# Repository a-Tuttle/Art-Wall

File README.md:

# Wall-Art

## software
Software for the Wall-Art controllers.

## hardware
Sketches for printing PCBs.

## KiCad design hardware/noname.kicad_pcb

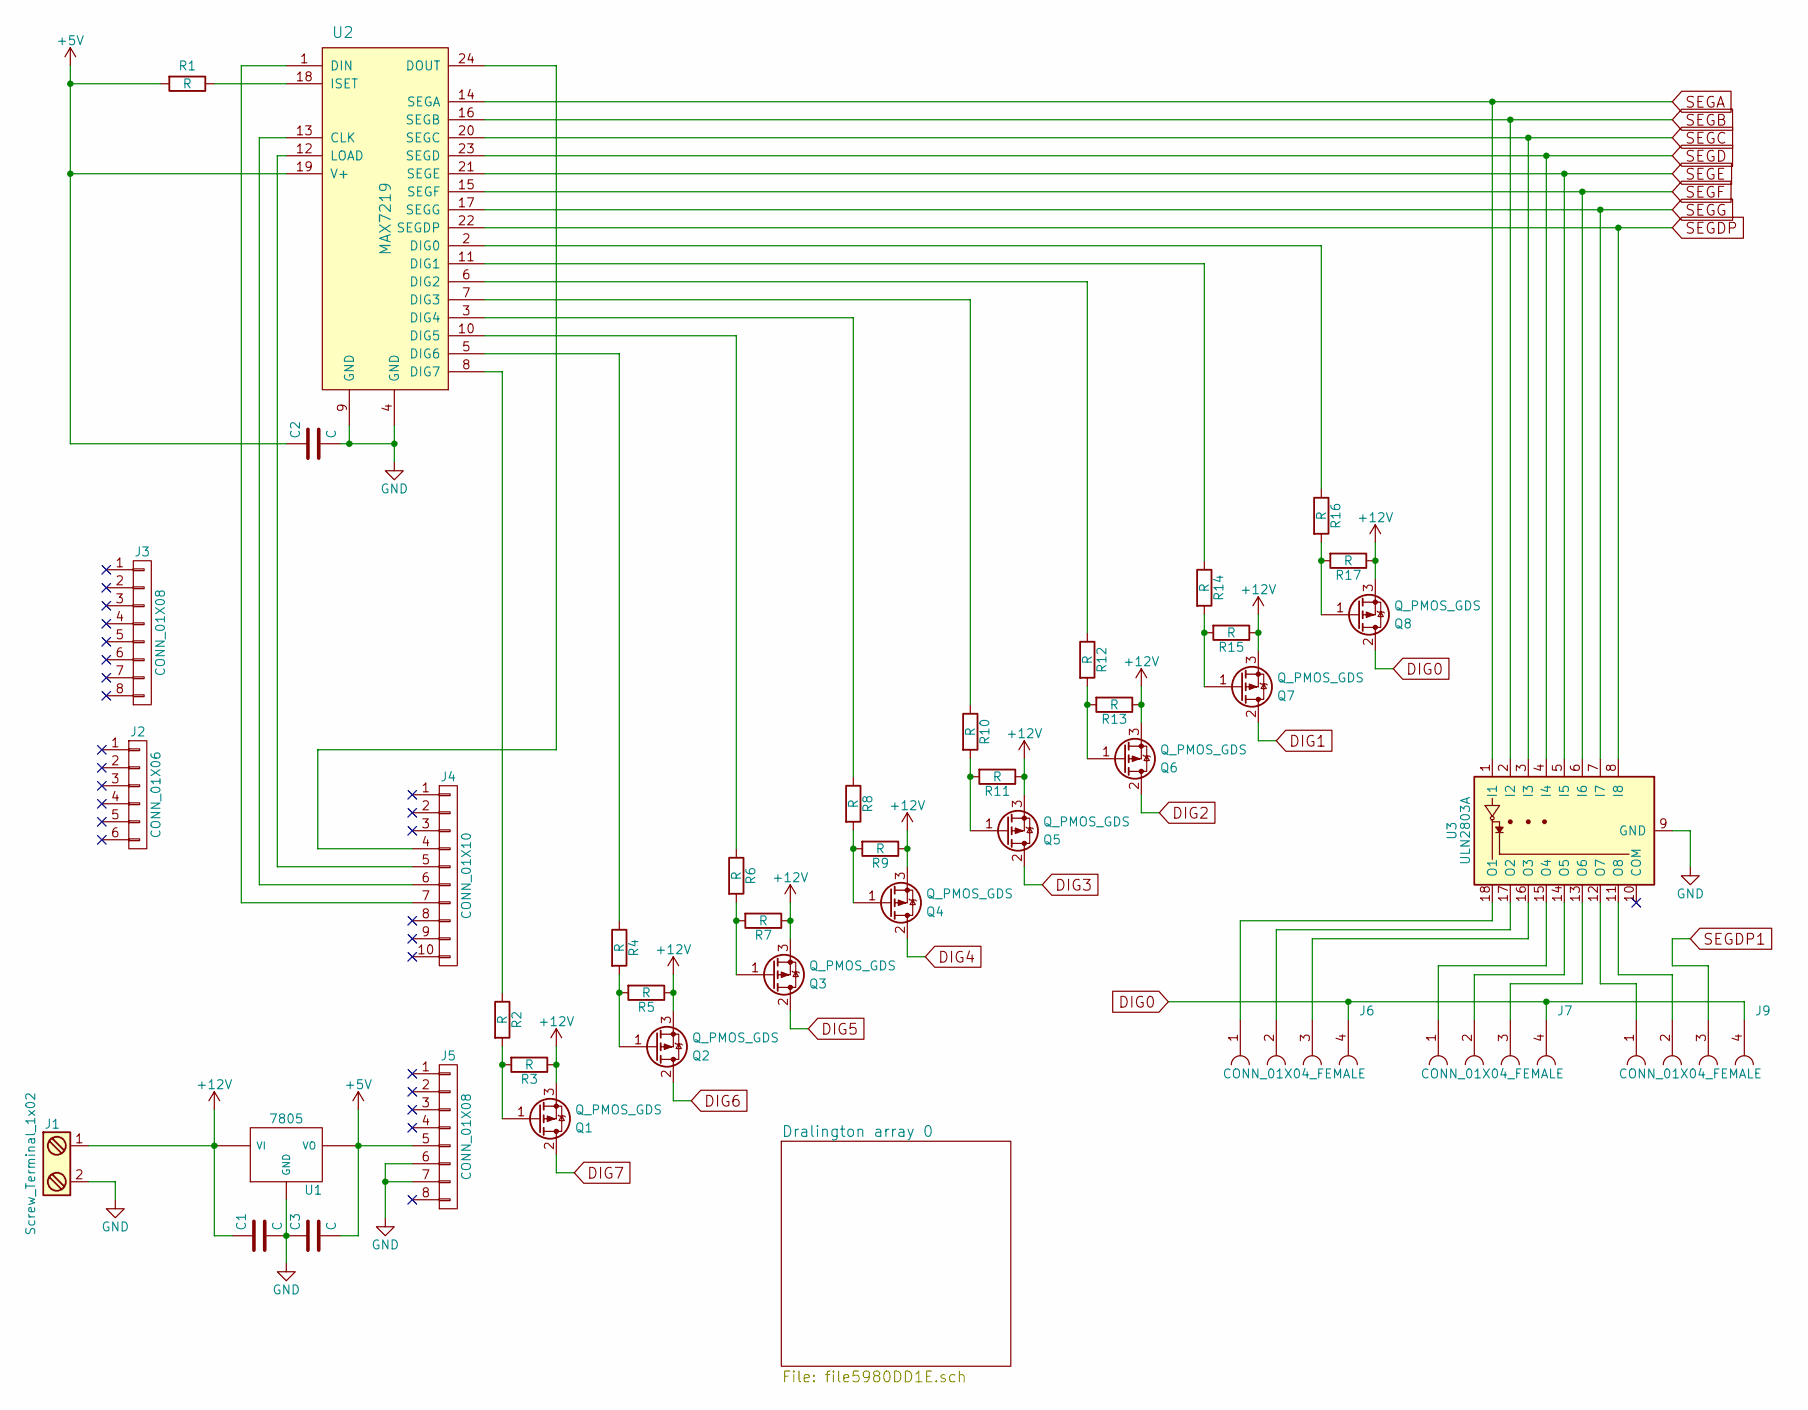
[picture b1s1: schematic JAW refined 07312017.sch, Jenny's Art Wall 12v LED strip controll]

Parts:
C1, C2, C3: C; C_Disc_D5.0mm_W2.5mm_P5.00mm
J1: Screw_Terminal_1x02; TerminalBlock_Philmore_TB132_02x5mm_Straight_power
J2: CONN_01X06; Pin_Header_Straight_1x06_Pitch2.54mm
J3, J5: CONN_01X08; Pin_Header_Straight_1x08_Pitch2.54mm
J4: CONN_01X10; Pin_Header_Straight_1x10_Pitch2.54mm
J6, J7, J9: CONN_01X04_FEMALE; Socket_Strip_Straight_1x04_Pitch2.54mm
Q1, Q2, Q3, Q4, Q5, Q6, Q7, Q8: Q_PMOS_GDS; TO-220
R1, R3, R5, R7, R9, R11, R13, R15, R17: R; R_Axial_DIN0309_L9.0mm_D3.2mm_P12.70mm_Horizontal
R2: R; R_Axial_DIN0207_L6.3mm_D2.5mm_P10.16mm_Horizontal
R4: R; R_Axial_DIN0204_L3.6mm_D1.6mm_P7.62mm_Horizontal
R6, R8, R10, R12, R14, R16: R; R_Axial_DIN0204_L3.6mm_D1.6mm_P5.08mm_Horizontal
U1: 7805; TO-220
U2: MAX7219; DIP-24_W7.62mm
U3: ULN2803A; DIP-18_W7.62mm

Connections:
+5V: C2.1, C3.2, J5.5, R1.2, U1.VO, U2.19 (V+)
+12V: C1.1, J1.1 (+), Q1.3 (S), Q2.3 (S), Q3.3 (S), Q4.3 (S), Q5.3 (S), Q6.3 (S), Q7.3 (S), Q8.3 (S), R3.1, R5.1, R7.1, R9.1, R11.1, R13.1, R15.1, R17.1, U1.VI
DIG0: J6.4, J7.4, J9.4, Q8.2 (D)
DIG1: Q7.2 (D); also elsewhere on the board
DIG2: Q6.2 (D); also elsewhere on the board
DIG3: Q5.2 (D); also elsewhere on the board
DIG4: Q4.2 (D); also elsewhere on the board
DIG5: Q3.2 (D); also elsewhere on the board
DIG6: Q2.2 (D); also elsewhere on the board
DIG7: Q1.2 (D); also elsewhere on the board
GND: C1.2, C2.2, C3.1, J1.2 (-), J5.6, J5.7, U1.GND, U2.4 (GND), U2.9 (GND), U3.9 (GND); also elsewhere on the board
unnamed: J4.5, U2.12 (LOAD)
unnamed: J4.6, U2.13 (CLK)
unnamed: J4.7, U2.1 (DIN)
unnamed: J6.1, U3.18 (O1)
unnamed: J6.2, U3.17 (O2)
unnamed: J6.3, U3.16 (O3)
unnamed: J7.1, U3.15 (O4)
unnamed: J7.2, U3.14 (O5)
unnamed: J7.3, U3.13 (O6)
unnamed: J9.1, U3.12 (O7)
unnamed: J9.2, U3.11 (O8)
unnamed: Q1.1 (G), R2.2, R3.2
unnamed: Q2.1 (G), R4.2, R5.2
unnamed: Q3.1 (G), R6.2, R7.2
unnamed: Q4.1 (G), R8.2, R9.2
unnamed: Q5.1 (G), R10.2, R11.2
unnamed: Q6.1 (G), R12.2, R13.2
unnamed: Q7.1 (G), R14.2, R15.2
unnamed: Q8.1 (G), R16.2, R17.2
unnamed: R1.1, U2.18 (ISET)
unnamed: R2.1, U2.8 (DIG7)
unnamed: R4.1, U2.5 (DIG6)
unnamed: R6.1, U2.10 (DIG5)
unnamed: R8.1, U2.3 (DIG4)
unnamed: R10.1, U2.7 (DIG3)
unnamed: R12.1, U2.6 (DIG2)
unnamed: R14.1, U2.11 (DIG1)
unnamed: R16.1, U2.2 (DIG0)
SEGA: U2.14 (SEGA), U3.1 (I1); also elsewhere on the board
SEGB: U2.16 (SEGB), U3.2 (I2); also elsewhere on the board
SEGC: U2.20 (SEGC), U3.3 (I3); also elsewhere on the board
SEGD: U2.23 (SEGD), U3.4 (I4); also elsewhere on the board
SEGDP: U2.22 (SEGDP), U3.8 (I8); also elsewhere on the board
SEGDP1: J9.3; also elsewhere on the board
SEGE: U2.21 (SEGE), U3.5 (I5); also elsewhere on the board
SEGF: U2.15 (SEGF), U3.6 (I6); also elsewhere on the board
SEGG: U2.17 (SEGG), U3.7 (I7); also elsewhere on the board

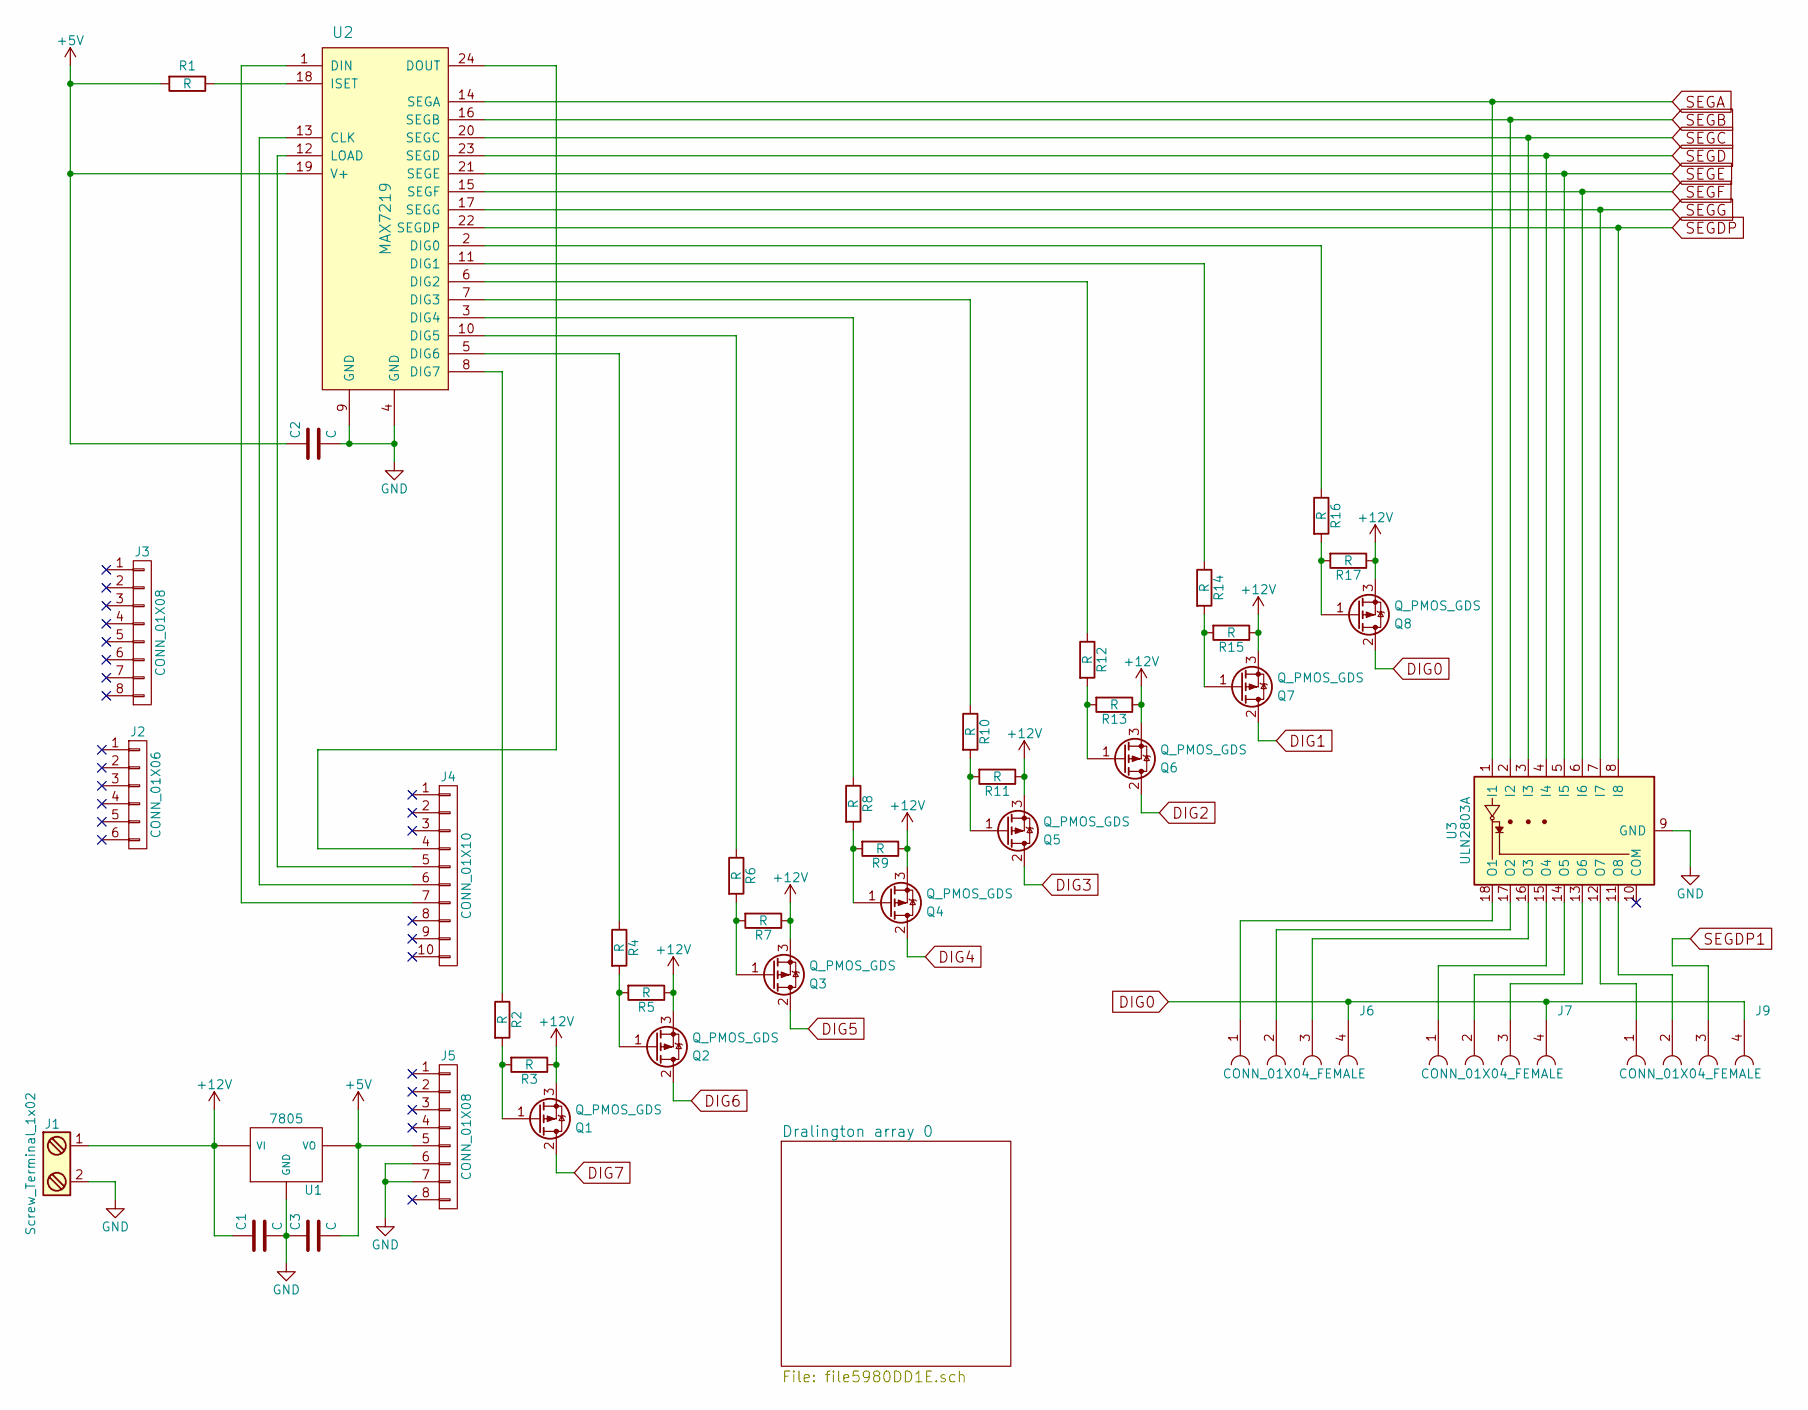
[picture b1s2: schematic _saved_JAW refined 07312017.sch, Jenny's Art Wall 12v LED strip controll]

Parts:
C1, C2, C3: C; C_Disc_D5.0mm_W2.5mm_P5.00mm
J1: Screw_Terminal_1x02; TerminalBlock_Philmore_TB132_02x5mm_Straight_power
J2: CONN_01X06; Pin_Header_Straight_1x06_Pitch2.54mm
J3, J5: CONN_01X08; Pin_Header_Straight_1x08_Pitch2.54mm
J4: CONN_01X10; Pin_Header_Straight_1x10_Pitch2.54mm
J6, J7, J9: CONN_01X04_FEMALE; Socket_Strip_Straight_1x04_Pitch2.54mm
Q1, Q2, Q3, Q4, Q5, Q6, Q7, Q8: Q_PMOS_GDS; TO-220
R1, R3, R5, R7, R9, R11, R13, R15, R17: R; R_Axial_DIN0309_L9.0mm_D3.2mm_P12.70mm_Horizontal
R2: R; R_Axial_DIN0207_L6.3mm_D2.5mm_P10.16mm_Horizontal
R4: R; R_Axial_DIN0204_L3.6mm_D1.6mm_P7.62mm_Horizontal
R6, R8, R10, R12, R14, R16: R; R_Axial_DIN0204_L3.6mm_D1.6mm_P5.08mm_Horizontal
U1: 7805; TO-220
U2: MAX7219; DIP-24_W7.62mm
U3: ULN2803A; DIP-18_W7.62mm

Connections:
+5V: C2.1, C3.2, J5.5, R1.2, U1.VO, U2.19 (V+)
+12V: C1.1, J1.1 (+), Q1.3 (S), Q2.3 (S), Q3.3 (S), Q4.3 (S), Q5.3 (S), Q6.3 (S), Q7.3 (S), Q8.3 (S), R3.1, R5.1, R7.1, R9.1, R11.1, R13.1, R15.1, R17.1, U1.VI
DIG0: J6.4, J7.4, J9.4, Q8.2 (D)
DIG1: Q7.2 (D); also elsewhere on the board
DIG2: Q6.2 (D); also elsewhere on the board
DIG3: Q5.2 (D); also elsewhere on the board
DIG4: Q4.2 (D); also elsewhere on the board
DIG5: Q3.2 (D); also elsewhere on the board
DIG6: Q2.2 (D); also elsewhere on the board
DIG7: Q1.2 (D); also elsewhere on the board
GND: C1.2, C2.2, C3.1, J1.2 (-), J5.6, J5.7, U1.GND, U2.4 (GND), U2.9 (GND), U3.9 (GND); also elsewhere on the board
unnamed: J4.5, U2.12 (LOAD)
unnamed: J4.6, U2.13 (CLK)
unnamed: J4.7, U2.1 (DIN)
unnamed: J6.1, U3.18 (O1)
unnamed: J6.2, U3.17 (O2)
unnamed: J6.3, U3.16 (O3)
unnamed: J7.1, U3.15 (O4)
unnamed: J7.2, U3.14 (O5)
unnamed: J7.3, U3.13 (O6)
unnamed: J9.1, U3.12 (O7)
unnamed: J9.2, U3.11 (O8)
unnamed: Q1.1 (G), R2.2, R3.2
unnamed: Q2.1 (G), R4.2, R5.2
unnamed: Q3.1 (G), R6.2, R7.2
unnamed: Q4.1 (G), R8.2, R9.2
unnamed: Q5.1 (G), R10.2, R11.2
unnamed: Q6.1 (G), R12.2, R13.2
unnamed: Q7.1 (G), R14.2, R15.2
unnamed: Q8.1 (G), R16.2, R17.2
unnamed: R1.1, U2.18 (ISET)
unnamed: R2.1, U2.8 (DIG7)
unnamed: R4.1, U2.5 (DIG6)
unnamed: R6.1, U2.10 (DIG5)
unnamed: R8.1, U2.3 (DIG4)
unnamed: R10.1, U2.7 (DIG3)
unnamed: R12.1, U2.6 (DIG2)
unnamed: R14.1, U2.11 (DIG1)
unnamed: R16.1, U2.2 (DIG0)
SEGA: U2.14 (SEGA), U3.1 (I1); also elsewhere on the board
SEGB: U2.16 (SEGB), U3.2 (I2); also elsewhere on the board
SEGC: U2.20 (SEGC), U3.3 (I3); also elsewhere on the board
SEGD: U2.23 (SEGD), U3.4 (I4); also elsewhere on the board
SEGDP: U2.22 (SEGDP), U3.8 (I8); also elsewhere on the board
SEGDP1: J9.3; also elsewhere on the board
SEGE: U2.21 (SEGE), U3.5 (I5); also elsewhere on the board
SEGF: U2.15 (SEGF), U3.6 (I6); also elsewhere on the board
SEGG: U2.17 (SEGG), U3.7 (I7); also elsewhere on the board

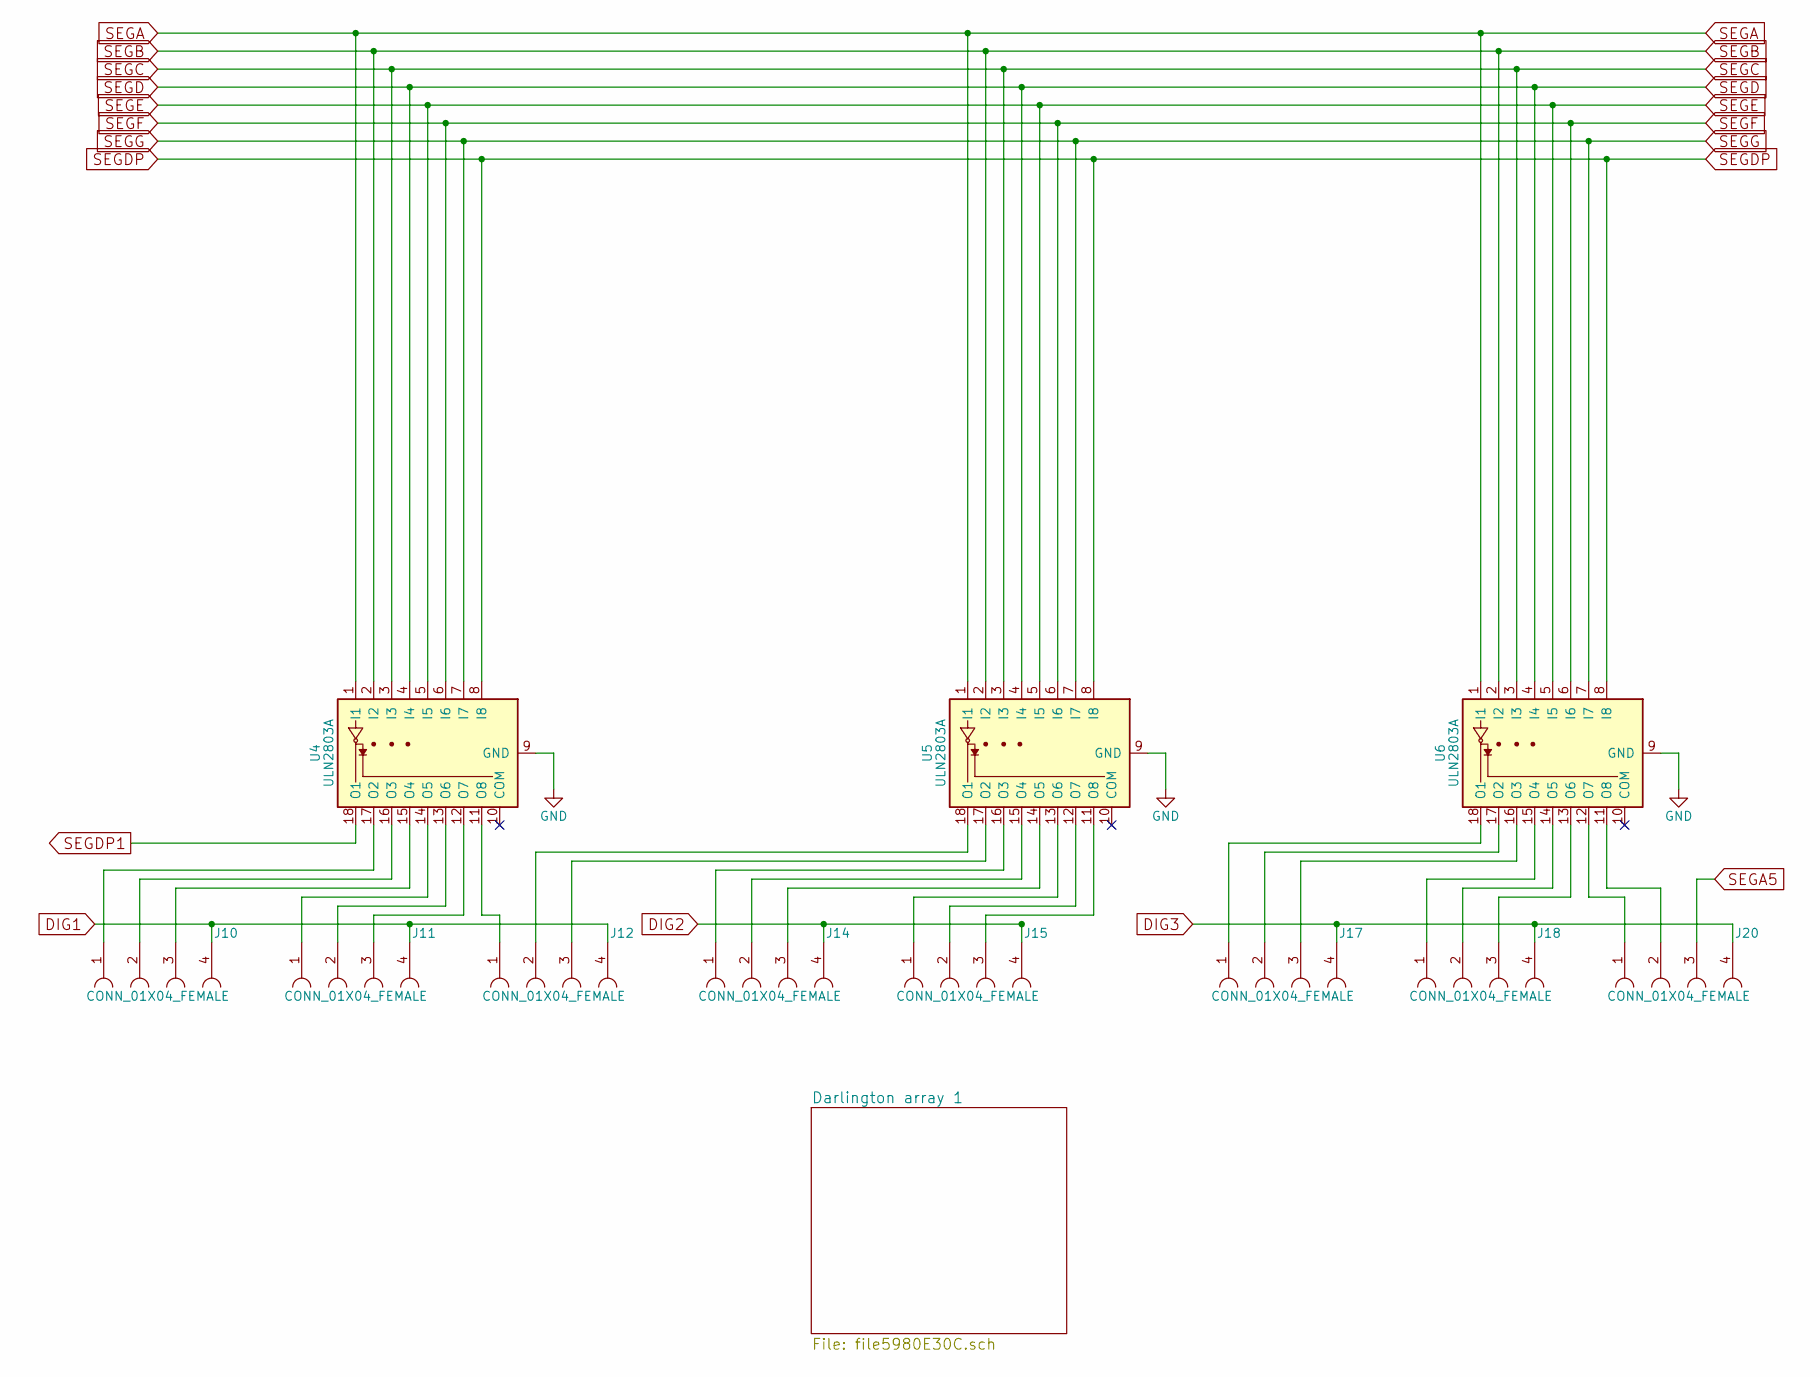
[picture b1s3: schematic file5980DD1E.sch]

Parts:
J10, J11, J12, J14, J15, J17, J18, J20: CONN_01X04_FEMALE; Socket_Strip_Straight_1x04_Pitch2.54mm
U4, U5, U6: ULN2803A; DIP-18_W7.62mm

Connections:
DIG1: J10.4, J11.4, J12.4; also elsewhere on the board
DIG2: J14.4, J15.4; also elsewhere on the board
DIG3: J17.4, J18.4, J20.4; also elsewhere on the board
GND: U4.9 (GND), U5.9 (GND), U6.9 (GND); also elsewhere on the board
unnamed: J10.1, U4.17 (O2)
unnamed: J10.2, U4.16 (O3)
unnamed: J10.3, U4.15 (O4)
unnamed: J11.1, U4.14 (O5)
unnamed: J11.2, U4.13 (O6)
unnamed: J11.3, U4.12 (O7)
unnamed: J12.1, U4.11 (O8)
unnamed: J12.2, U5.18 (O1)
unnamed: J12.3, U5.17 (O2)
unnamed: J14.1, U5.16 (O3)
unnamed: J14.2, U5.15 (O4)
unnamed: J14.3, U5.14 (O5)
unnamed: J15.1, U5.13 (O6)
unnamed: J15.2, U5.12 (O7)
unnamed: J15.3, U5.11 (O8)
unnamed: J17.1, U6.18 (O1)
unnamed: J17.2, U6.17 (O2)
unnamed: J17.3, U6.16 (O3)
unnamed: J18.1, U6.15 (O4)
unnamed: J18.2, U6.14 (O5)
unnamed: J18.3, U6.13 (O6)
unnamed: J20.1, U6.12 (O7)
unnamed: J20.2, U6.11 (O8)
SEGA: U4.1 (I1), U5.1 (I1), U6.1 (I1); also elsewhere on the board
SEGA5: J20.3; also elsewhere on the board
SEGB: U4.2 (I2), U5.2 (I2), U6.2 (I2); also elsewhere on the board
SEGC: U4.3 (I3), U5.3 (I3), U6.3 (I3); also elsewhere on the board
SEGD: U4.4 (I4), U5.4 (I4), U6.4 (I4); also elsewhere on the board
SEGDP: U4.8 (I8), U5.8 (I8), U6.8 (I8); also elsewhere on the board
SEGDP1: U4.18 (O1); also elsewhere on the board
SEGE: U4.5 (I5), U5.5 (I5), U6.5 (I5); also elsewhere on the board
SEGF: U4.6 (I6), U5.6 (I6), U6.6 (I6); also elsewhere on the board
SEGG: U4.7 (I7), U5.7 (I7), U6.7 (I7); also elsewhere on the board

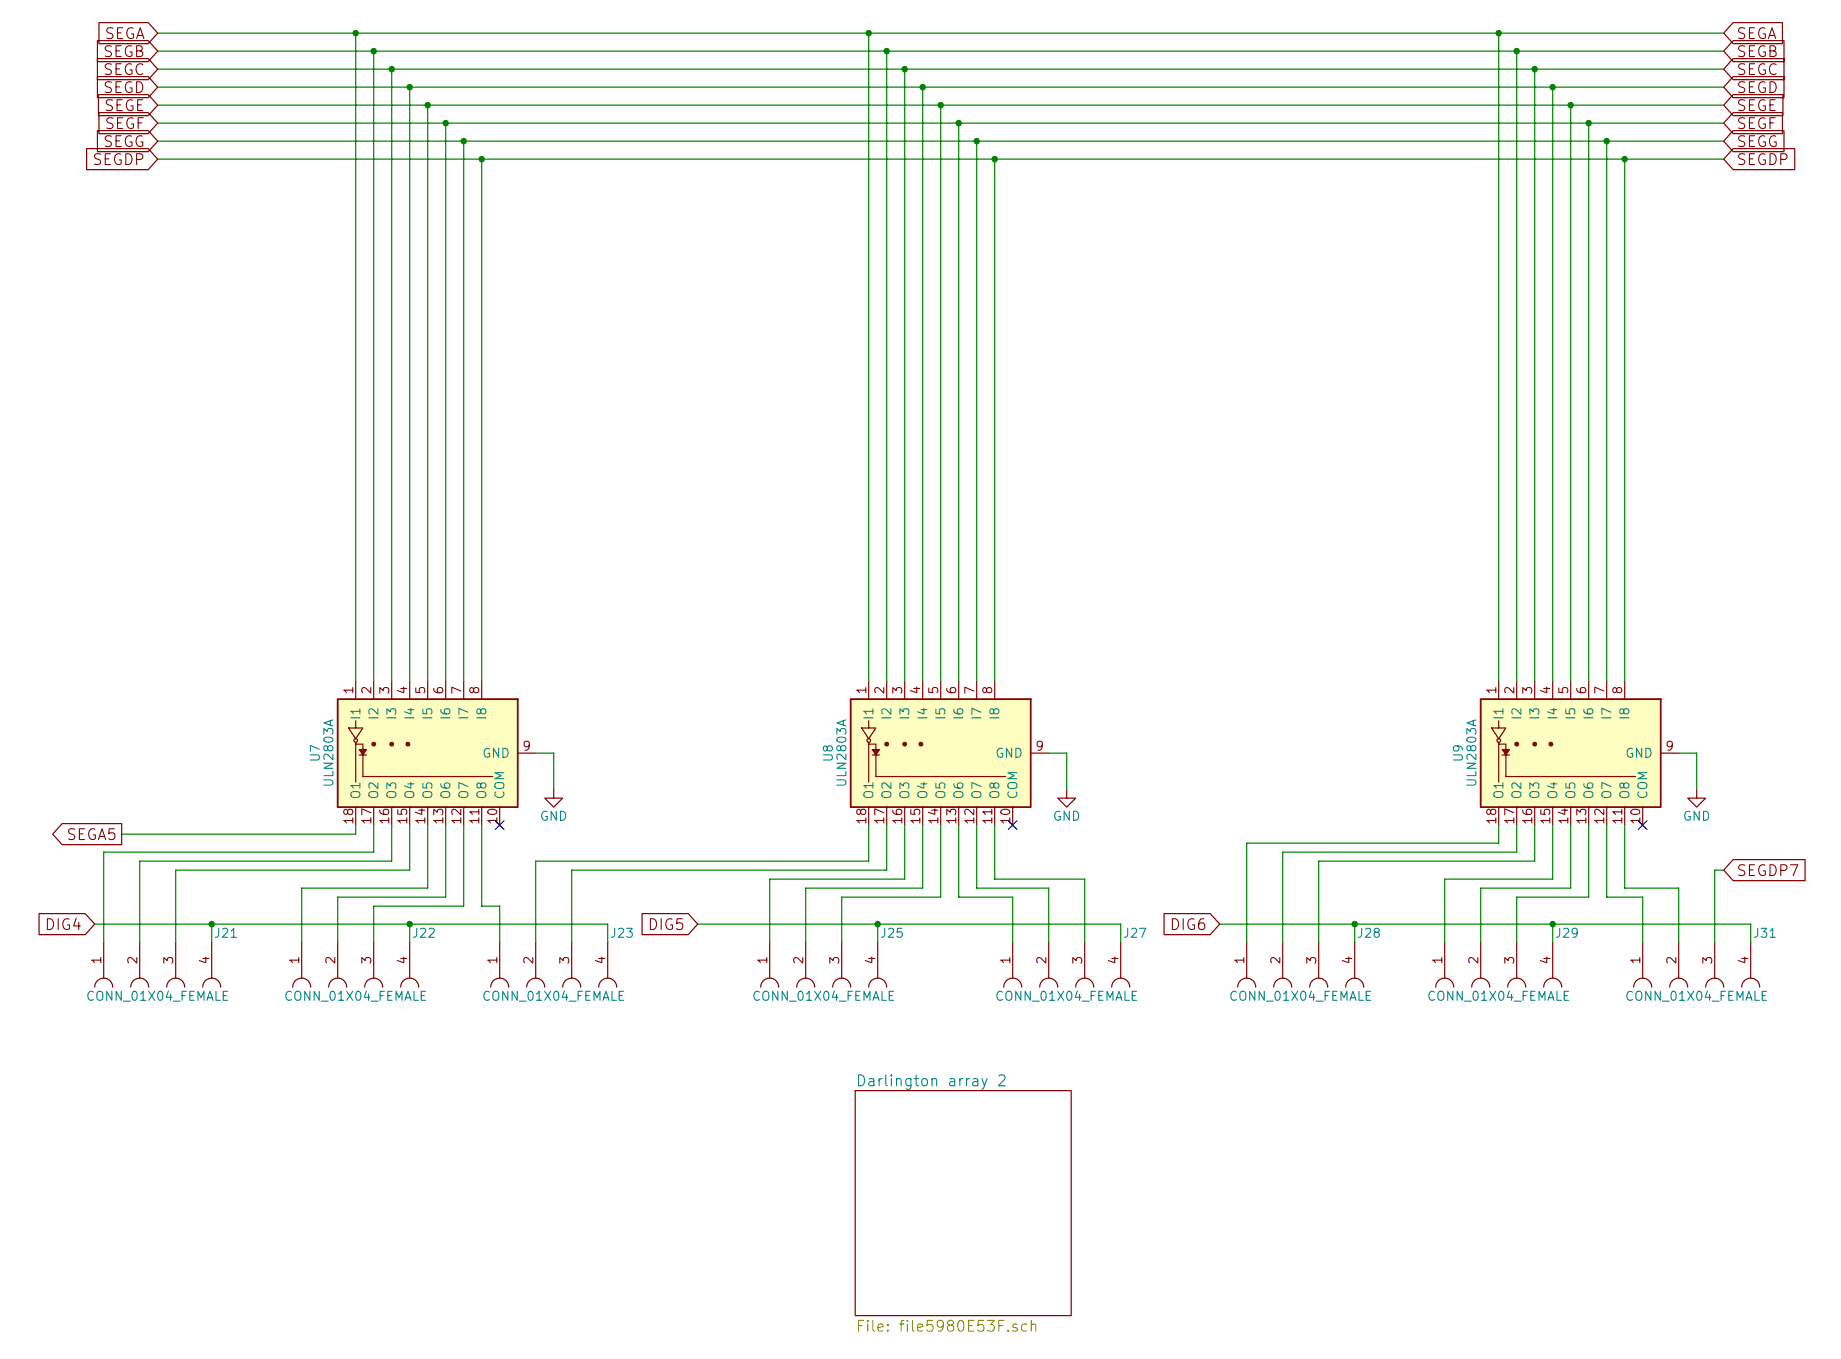
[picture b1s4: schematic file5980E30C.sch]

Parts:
J21, J22, J23, J25, J27, J28, J29, J31: CONN_01X04_FEMALE; Socket_Strip_Straight_1x04_Pitch2.54mm
U7, U8, U9: ULN2803A; DIP-18_W7.62mm

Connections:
DIG4: J21.4, J22.4, J23.4; also elsewhere on the board
DIG5: J25.4, J27.4; also elsewhere on the board
DIG6: J28.4, J29.4, J31.4; also elsewhere on the board
GND: U7.9 (GND), U8.9 (GND), U9.9 (GND); also elsewhere on the board
unnamed: J21.1, U7.17 (O2)
unnamed: J21.2, U7.16 (O3)
unnamed: J21.3, U7.15 (O4)
unnamed: J22.1, U7.14 (O5)
unnamed: J22.2, U7.13 (O6)
unnamed: J22.3, U7.12 (O7)
unnamed: J23.1, U7.11 (O8)
unnamed: J23.2, U8.18 (O1)
unnamed: J23.3, U8.17 (O2)
unnamed: J25.1, U8.16 (O3)
unnamed: J25.2, U8.15 (O4)
unnamed: J25.3, U8.14 (O5)
unnamed: J27.1, U8.13 (O6)
unnamed: J27.2, U8.12 (O7)
unnamed: J27.3, U8.11 (O8)
unnamed: J28.1, U9.18 (O1)
unnamed: J28.2, U9.17 (O2)
unnamed: J28.3, U9.16 (O3)
unnamed: J29.1, U9.15 (O4)
unnamed: J29.2, U9.14 (O5)
unnamed: J29.3, U9.13 (O6)
unnamed: J31.1, U9.12 (O7)
unnamed: J31.2, U9.11 (O8)
SEGA: U7.1 (I1), U8.1 (I1), U9.1 (I1); also elsewhere on the board
SEGA5: U7.18 (O1); also elsewhere on the board
SEGB: U7.2 (I2), U8.2 (I2), U9.2 (I2); also elsewhere on the board
SEGC: U7.3 (I3), U8.3 (I3), U9.3 (I3); also elsewhere on the board
SEGD: U7.4 (I4), U8.4 (I4), U9.4 (I4); also elsewhere on the board
SEGDP: U7.8 (I8), U8.8 (I8), U9.8 (I8); also elsewhere on the board
SEGDP7: J31.3; also elsewhere on the board
SEGE: U7.5 (I5), U8.5 (I5), U9.5 (I5); also elsewhere on the board
SEGF: U7.6 (I6), U8.6 (I6), U9.6 (I6); also elsewhere on the board
SEGG: U7.7 (I7), U8.7 (I7), U9.7 (I7); also elsewhere on the board

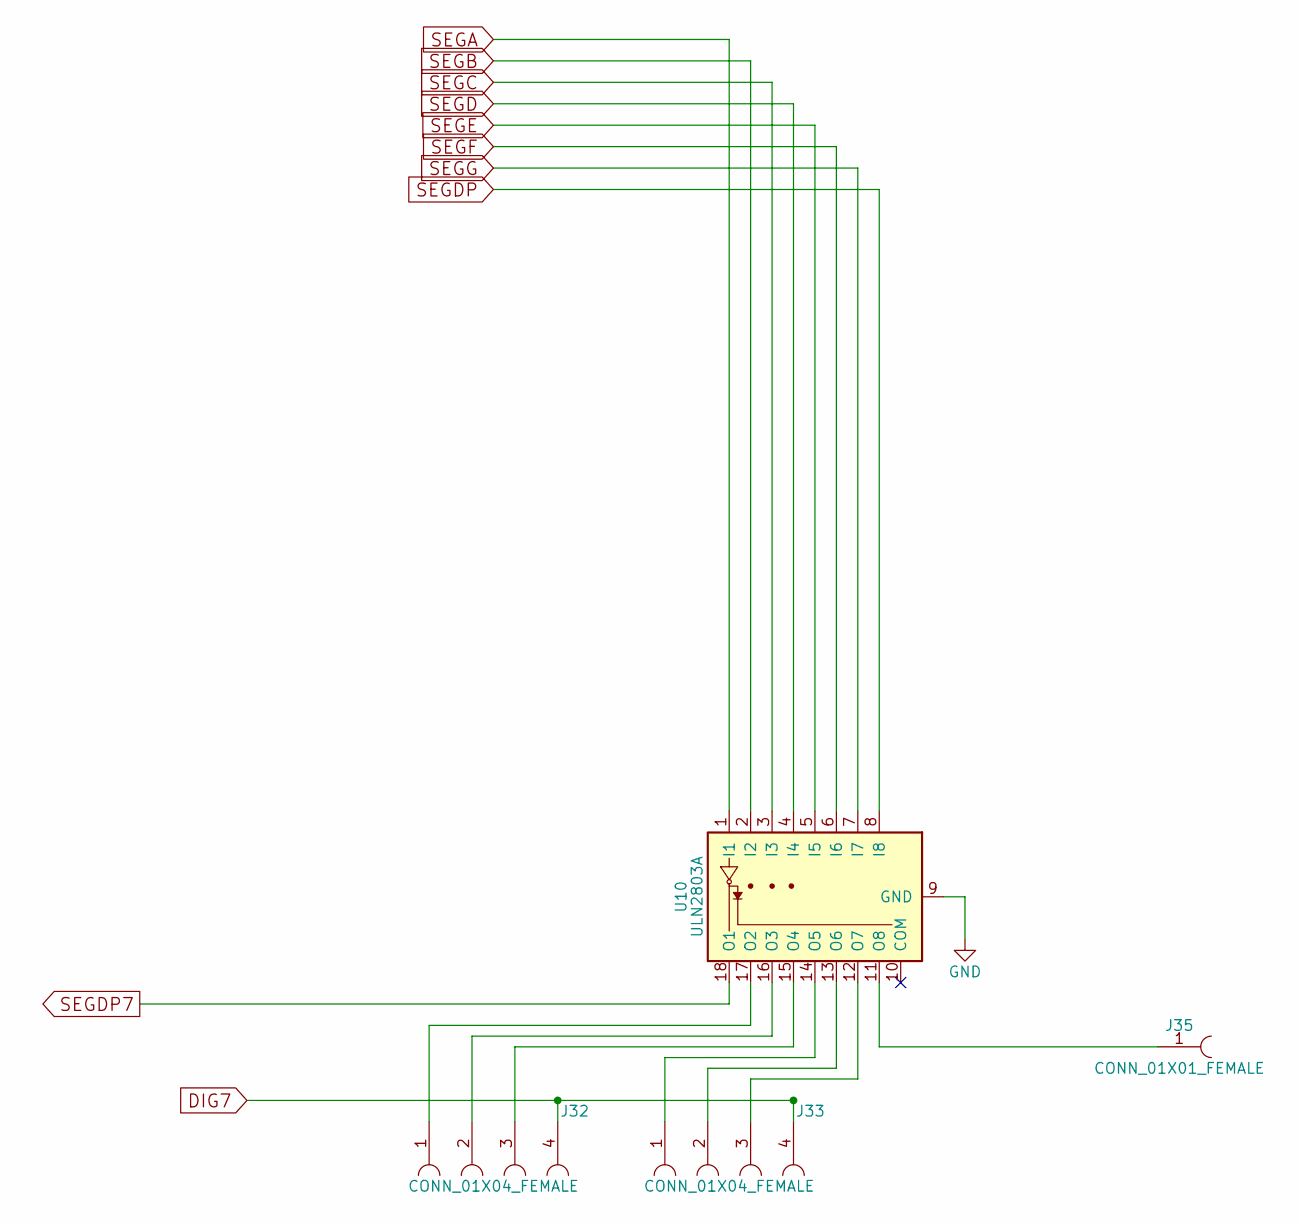
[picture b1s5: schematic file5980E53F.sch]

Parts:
J32, J33: CONN_01X04_FEMALE; Socket_Strip_Straight_1x04_Pitch2.54mm
J35: CONN_01X01_FEMALE; Socket_Strip_Straight_1x01_Pitch2.54mm
U10: ULN2803A; DIP-18_W7.62mm

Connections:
DIG7: J32.4, J33.4; also elsewhere on the board
GND: U10.9 (GND); also elsewhere on the board
unnamed: J32.1, U10.17 (O2)
unnamed: J32.2, U10.16 (O3)
unnamed: J32.3, U10.15 (O4)
unnamed: J33.1, U10.14 (O5)
unnamed: J33.2, U10.13 (O6)
unnamed: J33.3, U10.12 (O7)
unnamed: J35.1, U10.11 (O8)
SEGA: U10.1 (I1); also elsewhere on the board
SEGB: U10.2 (I2); also elsewhere on the board
SEGC: U10.3 (I3); also elsewhere on the board
SEGD: U10.4 (I4); also elsewhere on the board
SEGDP: U10.8 (I8); also elsewhere on the board
SEGDP7: U10.18 (O1); also elsewhere on the board
SEGE: U10.5 (I5); also elsewhere on the board
SEGF: U10.6 (I6); also elsewhere on the board
SEGG: U10.7 (I7); also elsewhere on the board

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
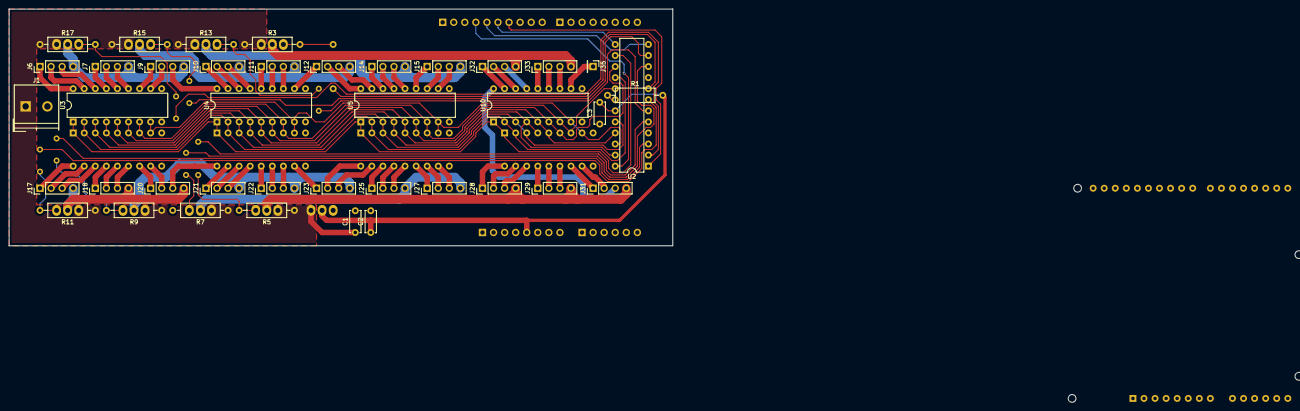
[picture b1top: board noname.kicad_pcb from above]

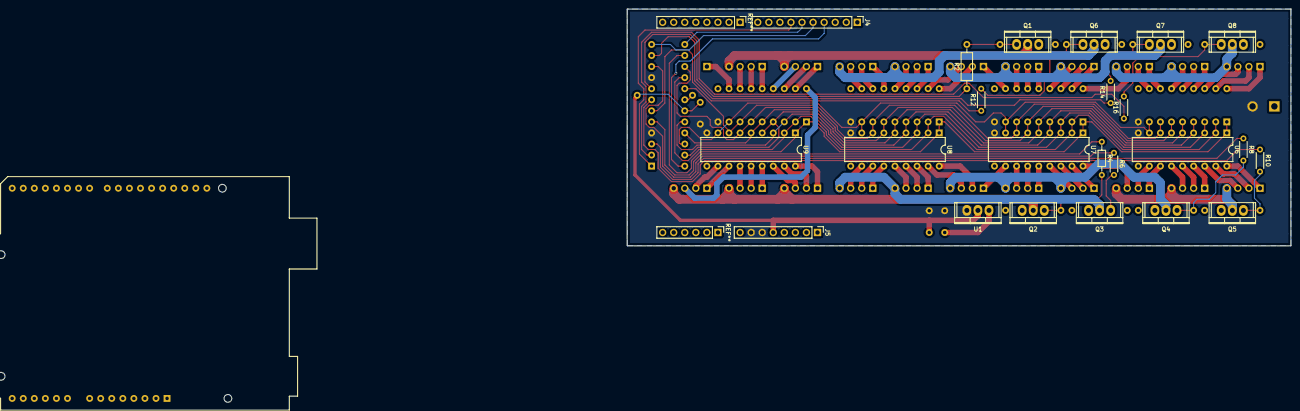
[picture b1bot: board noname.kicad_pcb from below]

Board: 2 copper layers, 152.4 x 54.4 mm, 63 parts (23 on the bottom side), 103 nets.

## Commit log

2017-10-31 initial
2017-10-31 move things around a bit
2017-10-31 add readme
2017-11-06 initkh
2017-11-06 wing proj files and notes
2017-11-12 added test
2017-11-19 test2
